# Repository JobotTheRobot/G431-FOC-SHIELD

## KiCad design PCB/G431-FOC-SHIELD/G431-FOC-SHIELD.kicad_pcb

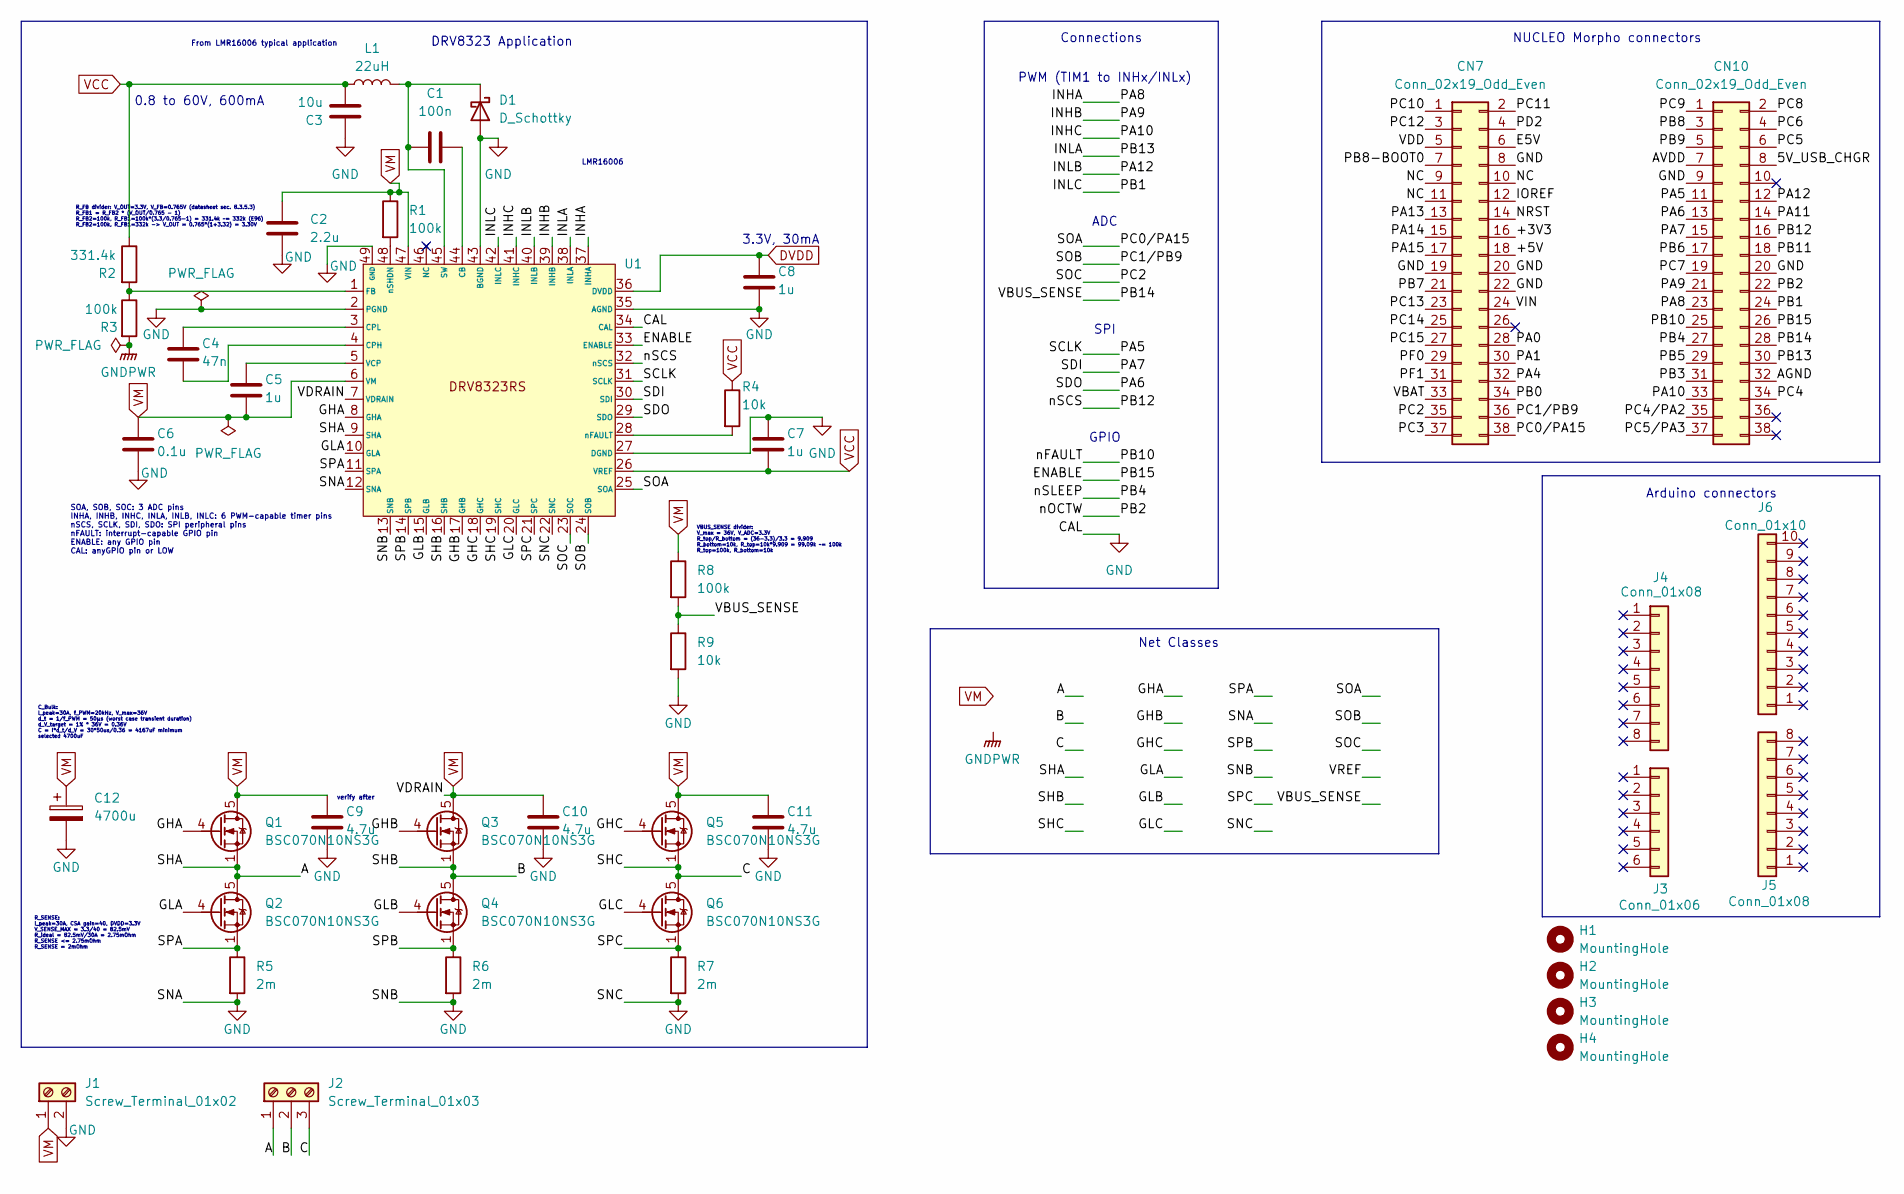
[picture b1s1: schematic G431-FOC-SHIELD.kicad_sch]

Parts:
C1: 100n; C_0603_1608Metric
C2: 2.2u; C_0805_2012Metric
C3: 10u; C_0805_2012Metric
C4: 47n; C_0805_2012Metric
C5, C7, C8: 1u; C_0603_1608Metric
C6: 0.1u; C_0603_1608Metric
C9, C10, C11: 4.7u; C_1210_3225Metric
C12: 4700u; CP_Radial_D16.0mm_P7.50mm
CN7, CN10: Conn_02x19_Odd_Even; PinSocket_2x19_P2.54mm_Vertical
D1: D_Schottky; D_SMA
H1, H2, H3, H4: MountingHole; MountingHole_3.2mm_M3
J1: Screw_Terminal_01x02; TerminalBlock_Phoenix_MKDS-1,5-2_1x02_P5.00mm_Horizontal
J2: Screw_Terminal_01x03; TerminalBlock_Phoenix_MKDS-1,5-3_1x03_P5.00mm_Horizontal
J3: Conn_01x06; PinHeader_1x06_P2.54mm_Vertical
J4, J5: Conn_01x08; PinHeader_1x08_P2.54mm_Vertical
J6: Conn_01x10; PinHeader_1x10_P2.54mm_Vertical
L1: 22uH; L_1210_3225Metric
Q1, Q2, Q3, Q4, Q5, Q6: BSC070N10NS3G; TDSON-8-1
R1, R3, R8: 100k; R_0603_1608Metric
R2: 331.4k; R_0603_1608Metric
R4, R9: 10k; R_0603_1608Metric
R5, R6, R7: 2m; R_2512_6332Metric
U1: DRV8323RSRGZR; QFN50P700X700X100-49N; PARTREV C

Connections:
/5V_USB_CHGR: CN10.8
/+3V3: CN7.16
/+5V: CN7.18
/A: J2.1, Q1.1 (S), Q1.2 (S), Q1.3 (S), Q2.5 (D), U1.9 (SHA)
/AGND: CN10.32
/AVDD: CN10.7
/B: J2.2, Q3.1 (S), Q3.2 (S), Q3.3 (S), Q4.5 (D), U1.16 (SHB)
/C: J2.3, Q5.1 (S), Q5.2 (S), Q5.3 (S), Q6.5 (D), U1.19 (SHC)
/E5V: CN7.6
/ENABLE: CN10.26, U1.33 (ENABLE)
/GHA: Q1.4 (G), U1.8 (GHA)
/GHB: Q3.4 (G), U1.17 (GHB)
/GHC: Q5.4 (G), U1.18 (GHC)
/GLA: Q2.4 (G), U1.10 (GLA)
/GLB: Q4.4 (G), U1.15 (GLB)
/GLC: Q6.4 (G), U1.20 (GLC)
/INHA: CN10.23, U1.37 (INHA)
/INHB: CN10.21, U1.39 (INHB)
/INHC: CN10.33, U1.41 (INHC)
/INLA: CN10.30, U1.38 (INLA)
/INLB: CN10.12, U1.40 (INLB)
/INLC: CN10.24, U1.42 (INLC)
/IOREF: CN7.12
/NC: CN7.9, CN7.10, CN7.11
/NRST: CN7.14
/PA0: CN7.28
/PA1: CN7.30
/PA4: CN7.32
/PA5: CN10.11, U1.31 (SCLK)
/PA6: CN10.13, U1.29 (SDO)
/PA7: CN10.15, U1.30 (SDI)
/PA11: CN10.14
/PA13: CN7.13
/PA14: CN7.15
/PA15: CN7.17
/PB0: CN7.34
/PB2: CN10.22
/PB3: CN10.31
/PB4: CN10.27
/PB5: CN10.29
/PB6: CN10.17
/PB7: CN7.21
/PB8: CN10.3
/PB8-BOOT0: CN7.7
/PB9: CN10.5
/PB10: CN10.25
/PB11: CN10.18
/PB12: CN10.16, U1.32 (nSCS)
/PB14: CN10.28, R8.2, R9.1
/PC0/PA15: CN7.38, U1.25 (SOA)
/PC1/PB9: CN7.36, U1.24 (SOB)
/PC2: CN7.35, U1.23 (SOC)
/PC3: CN7.37
/PC4: CN10.34
/PC4/PA2: CN10.35
/PC5: CN10.6
/PC5/PA3: CN10.37
/PC6: CN10.4
/PC7: CN10.19
/PC8: CN10.2
/PC9: CN10.1
/PC10: CN7.1
/PC11: CN7.2
/PC12: CN7.3
/PC13: CN7.23
/PC14: CN7.25
/PC15: CN7.27
/PD2: CN7.4
/PF0: CN7.29
/PF1: CN7.31
/SPA: Q2.1 (S), Q2.2 (S), Q2.3 (S), R5.1, U1.11 (SPA)
/SPB: Q4.1 (S), Q4.2 (S), Q4.3 (S), R6.1, U1.14 (SPB)
/SPC: Q6.1 (S), Q6.2 (S), Q6.3 (S), R7.1, U1.21 (SPC)
/VBAT: CN7.33
/VDD: CN7.5
/VIN: CN7.24
DVDD: C8.1, U1.36 (DVDD)
GND: C2.2, C3.2, C6.2, C7.1, C8.2, C9.2, C10.2, C11.2, C12.2, CN7.8, CN7.19, CN7.20, CN7.22, CN10.9, CN10.20, D1.2 (A), J1.2, R5.2, R6.2, R7.2, R9.2, U1.2 (PGND), U1.12 (SNA), U1.13 (SNB), U1.22 (SNC), U1.27 (DGND), U1.34 (CAL), U1.35 (AGND), U1.43 (BGND), U1.49 (GND)
GNDPWR: R3.2
unnamed: C1.1, D1.1 (K), L1.2, U1.45 (SW)
unnamed: C1.2, U1.44 (CB)
unnamed: C4.2, U1.4 (CPH)
unnamed: C4.1, U1.3 (CPL)
unnamed: R2.2, R3.1, U1.1 (FB)
unnamed: C5.1, U1.5 (VCP)
unnamed: R4.2, U1.28 (nFAULT)
unnamed: R1.2, U1.48 (nSHDN)
VCC: C3.1, C7.2, L1.1, R2.1, R4.1, U1.26 (VREF)
VM: C2.1, C5.2, C6.1, C9.1, C10.1, C11.1, C12.1, J1.1, Q1.5 (D), Q3.5 (D), Q5.5 (D), R1.1, R8.1, U1.6 (VM), U1.7 (VDRAIN), U1.47 (VIN)

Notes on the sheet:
PWM (TIM1 to INHx/INLx)
NUCLEO Morpho connectors
Net Classes
From LMR16006 typical application
SOA, SOB, SOC: 3 ADC pins INHA, INHB, INHC, INLA, INLB, INLC: 6 PWM-capable timer pins nSCS, SCLK, SDI, SDO: SPI peripheral pins nFAULT: interrupt-capable GPIO pin ENABLE: any GPIO pin CAL: anyGPIO pin or LOW
VBUS_SENSE divider: V_max = 36V, V_ADC=3.3V R_top/R_bottom = (36-3.3)/3.3 = 9.909 R_bottom=10k, R_top=10k*9.909 = 99.09k ~= 100k R_top=100k, R_bottom=10k
0.8 to 60V, 600mA
SPI
R_FB divider: V_OUT=3.3V, V_FB=0.765V (datasheet sec. 8.3.5.3) R_FB1 = R_FB2 * (V_OUT/0.765 - 1) R_FB2=100k, R_FB1=100k*(3.3/0.765-1) = 331.4k ~= 332k (E96) R_FB2=100k, R_FB1=332k -> V_OUT = 0.765*(1+3.32) = 3.30V
C_Bulk: I_peak=30A, f_PWM=20kHz, V_max=36V d_t = 1/f_PWM = 50µs (worst case transient duration) d_V_target = 1% * 36V = 0.36V C = I*d_t/d_V = 30*50us/0.36 = 4167uF minimum selected 4700uF
R_SENSE: I_peak=30A, CSA gain=40, DVDD=3.3V V_SENSE_MAX = 3.3/40 = 82.5mV R_ideal = 82.5mV/30A = 2.75mOhm R_SENSE <= 2.75mOhm R_SENSE = 2mOhm
ADC
DRV8323 Application
3.3V, 30mA
verify after
Arduino connectors
LMR16006
Connections
GPIO

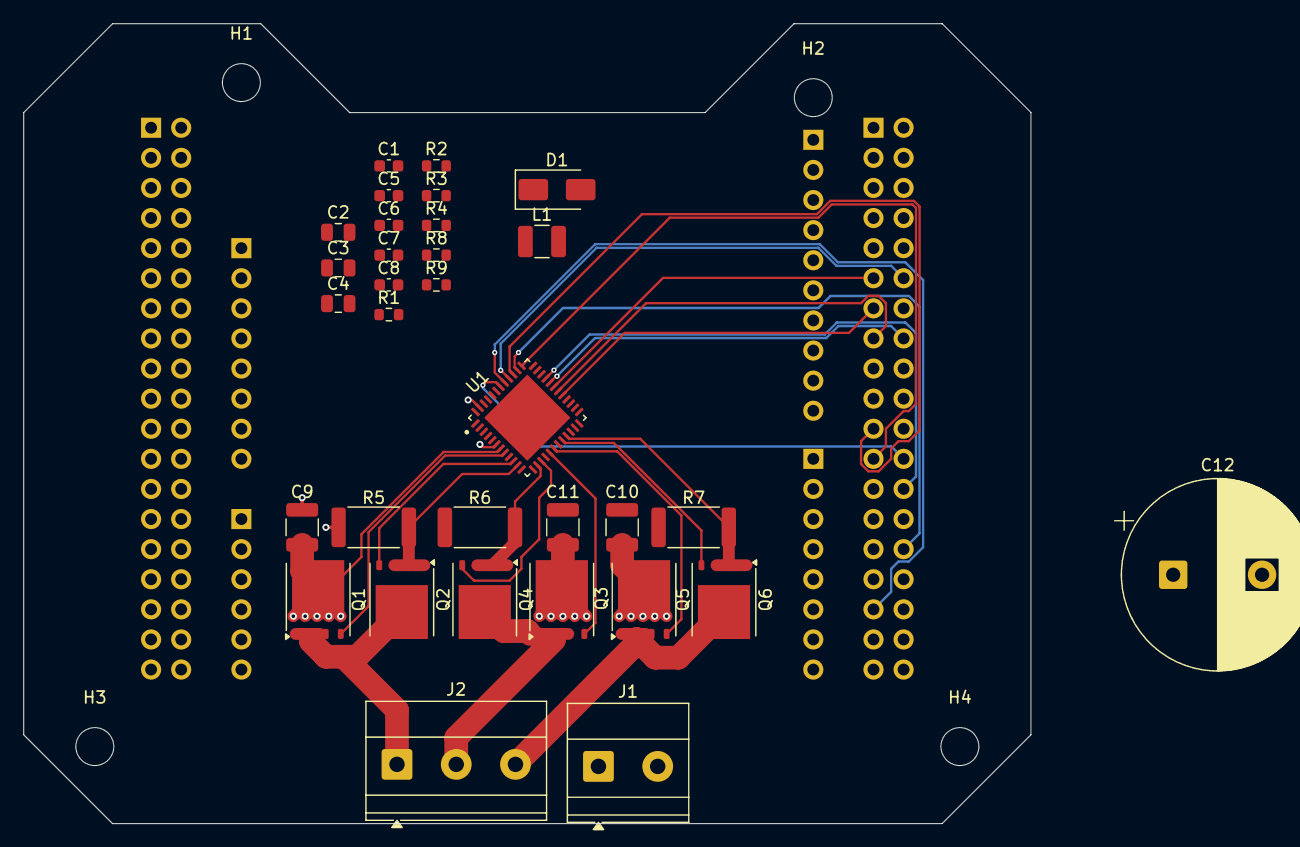
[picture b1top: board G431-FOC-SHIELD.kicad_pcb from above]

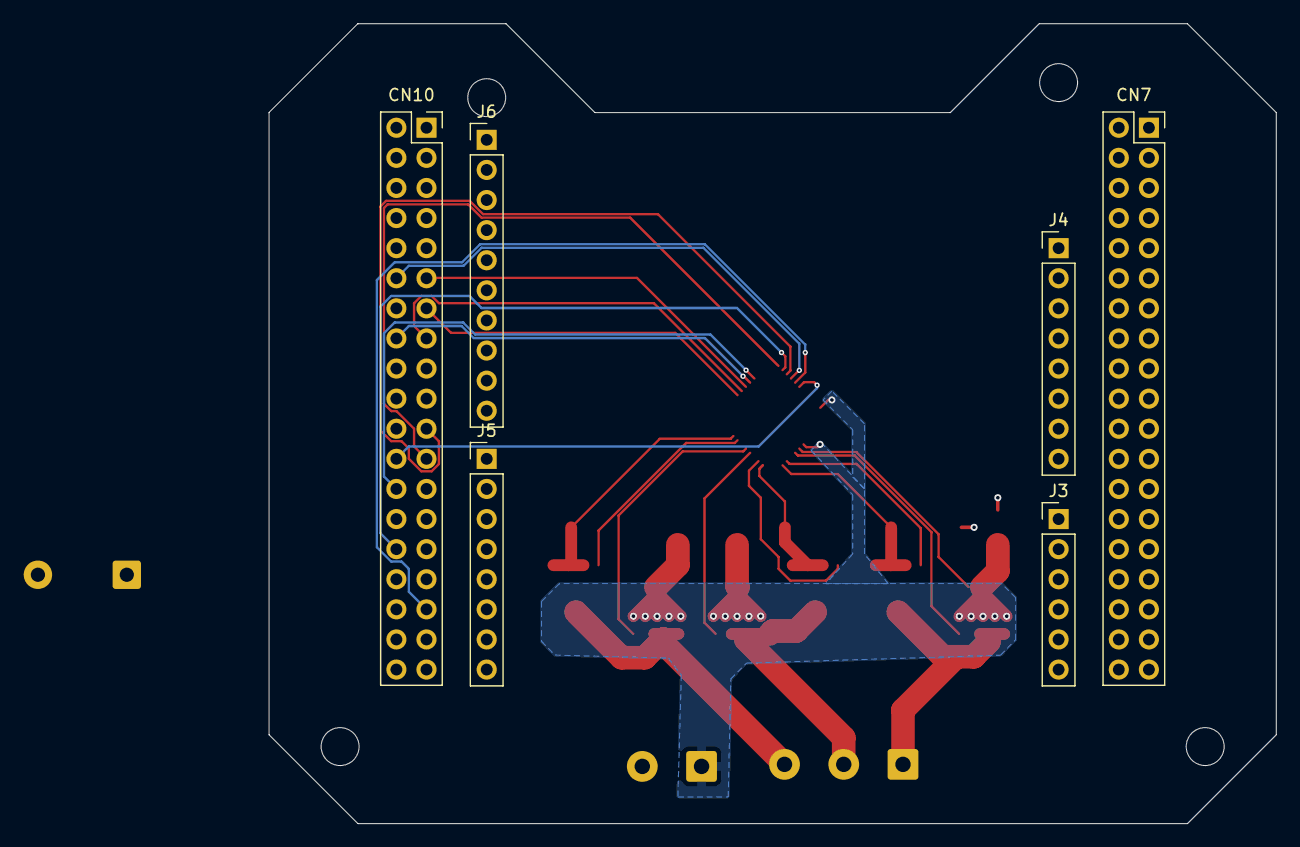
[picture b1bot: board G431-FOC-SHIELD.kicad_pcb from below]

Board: 4 copper layers, 85.0 x 67.5 mm, 42 parts (6 on the bottom side), 40 nets.

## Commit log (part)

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2025-10-20 project setup
2025-10-20 folder structure setup
2025-10-22 started FunctionalBlockDiagram
2025-11-03 block diagram
2025-12-26 added cubemx project
2025-12-30 started assigning pins properly
2026-02-01 restructuring
2026-03-27 started schematic design, added DRV8323 typical application
2026-04-01 started calculations python script
2026-04-01 calculations spreadsheet
2026-04-02 started schematic calculations
2026-05-17 calculations in schematic
2026-05-18 started layout
2026-05-19 4-layer stackup
2026-05-22 started placement
